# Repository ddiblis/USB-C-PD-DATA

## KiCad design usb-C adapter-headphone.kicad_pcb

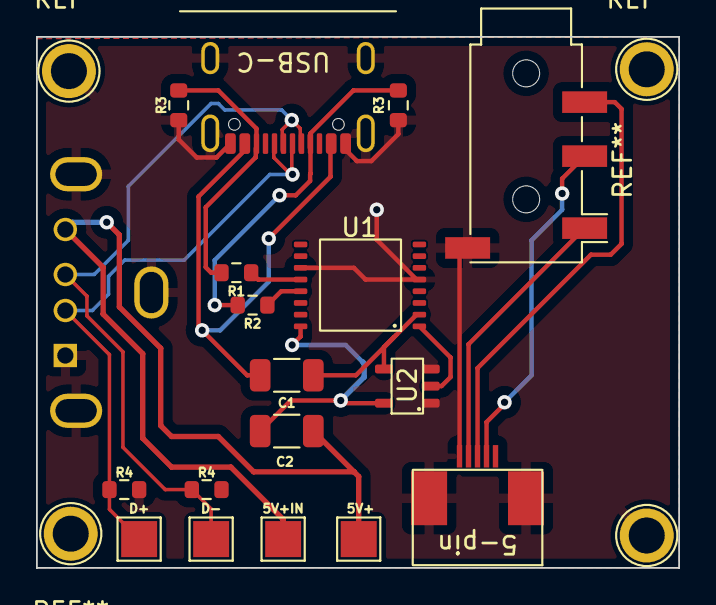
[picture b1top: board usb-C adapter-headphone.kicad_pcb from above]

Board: 2 copper layers, 35.7 x 29.5 mm, 17 parts (1 on the bottom side), 11 nets.

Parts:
5-pin: 5pin FPC
5V+, 5V+IN: TestPoint_Pad_2.0x2.0mm
C1, C2: C_1206_3216Metric
D+: TestPoint_Pad_2.0x2.0mm
D-: TestPoint_Pad_2.0x2.0mm
R1, R2, R3, R3#2, R4, R4#2: R_0603_1608Metric
U1: IP2721
U2: LND01
USB-A: USB_A_Molex_105057_Vertical
USB-C: usb-c f

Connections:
5V+: 5V+.1, 5V+IN.1, C2.2, USB-A.4
CC1: R2.1, R2.2, R3#2.1, U1.13, USB-C.6
CC2: R1.1, R1.2, R3.1, U1.12, USB-C.12
D+: D+.1, R4.1, USB-A.2, USB-C.8, USB-C.10
D-: D-.1, R4#2.1, USB-A.3, USB-C.7, USB-C.9
GND: 5-pin.1, 5-pin.2, 5-pin.7, R3.2, R3#2.2, R4.2, R4#2.2, U1.5, U1.11, USB-A.1, USB-A.5, USB-C.1, USB-C.4, USB-C.13
NC: U1.3, U1.4, U1.9, U1.10, U1.14, U1.15, U2.1, U2.3
TST: U1.6, U1.7, U1.8
VBUS: C1.1, C2.1, U1.16, U2.5, USB-C.2, USB-C.3
VBUSG: U1.1, U2.2
VIN: C1.2, U1.2, U2.4

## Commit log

2022-05-22 build(All-files): Build 1.0 of my USB-C PD and USB-C to USB-A data delivery as a sub device.
    BREAKING CHANGE:
2022-05-24 fix(all): combined pcbs
2022-05-24 feat(gerber-files): ready to upload for any pcb website
2022-05-25 fix(usb-c-adapter): Fixed issue of non grounded resistors
2022-05-25 feat(no-headphone-usb-c-adapter-shrunk-down): NA
2022-05-25 docs(Added-BOM): NA
2022-05-27 fix(BOM): BOM was incorrect
2022-05-28 build(2.0-build-with-reduced-size-and-cleaned-contact-points): no
2022-06-02 build(final-push): final push
